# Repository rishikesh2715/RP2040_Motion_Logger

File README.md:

# RP2040 Motion Logger

<p align="center">
  <div>

  </div>
  <div>

  </div>
</p>

*I have slightly modified the board to include a bootloader button and made some aesthetic changes since having this board produced. Thus, the produced board slightly looks different. Everything else remains the same*

## Order this Board Through [PCBway](https://www.pcbway.com) 🛫

You can order this board through PCBway for excellent board quality and fast shipping at a very affordable rate. 

- Using PCBway as the manufacturer is recommended because the stackup for this board is based on their specifications. The differential impedance for the USB differential pair has been calculated based on PCBway’s stackup, ensuring that the board will perform as intended when manufactured with them.

- The Bill of Materials (BOM) provided is in PCBway's format. This compatibility ensures a smooth and reliable production experience, reducing the chances of delays due to part sourcing.

To order, simply upload the zip file to PCBway’s portal, select your preferences,
set the Min Track/spacing to 6/6 mil and set the min hole size to 0.2mm. Choosing Immersion Gold(ENIG) as the board finish is recommended but not required, and place your order. PCBway’s user-friendly interface allows for easy customization and order tracking from manufacturing to delivery.

You can learn more about PCBway at the end.

## Interactive PCB Viewer

You can view this board interactively on [KiCanvas](https://kicanvas.org/?github=https%3A%2F%2Fgithub.com%2Frishikesh2715%2FRP2040_Motion_Logger).

## Overview
The RP2040 Motion Logger is a custom microcontroller board based on the RP2040 chip, designed for motion data logging and versatile IoT applications. This compact board (0.9 x 2.48 inches) integrates a wide range of features, making it a powerful tool for projects requiring motion sensing, storage, and connectivity.

### Key Features:
- **Microcontroller**: RP2040 with dual ARM Cortex M0+ processors
- **Motion Sensor**: ICM-42688-P IMU for 6-axis motion tracking
- **Storage**: 128 Mbit Quad SPI Flash Memory and SD Card connector
- **Power Options**: USB Type-C connector or 1S LiPo/Li-ion battery
- **Battery Management**: Onboard charger for 1S LiPo/Li-ion batteries
- **LEDs**: Addressable RGB LED for user indications, plus power status LEDs for both 3.3V and 5V
- **Connectors**:
  - TC2030 JTAG Connector for programming and debugging
  - A set of pin headers including UART, I2C, SPI, ADC, and GPIO pins
- **Power Supply**: 3.3V buck converter supporting up to 2A current
- **Additional Features**: Reset and Bootloader buttons, ESD protection, USB Power, Battery Power, and 3.3V Power pins on headers

### Power Options:
The RP2040 Motion Logger can be powered either via the USB Type-C connector or a 1S LiPo/Li-ion battery. 

### Programming Options:
You can program the board through the USB Type-C connector or the TC2030 JTAG Connector.

## Getting Started
1. **Power Up**: Connect the board via USB Type-C or connect a 1S LiPo/Li-ion battery.
2. **Programming**: Use either the USB connection or JTAG connector with an appropriate debugger to flash your code. (I use VS Code with Raspberry PI PICO Extension)
3. **Bootloader Mode**: Hold down the Bootloader button while connecting the board to USB to enter bootloader mode.
4. **Data Logging**: Use the IMU and available storage to log motion data, or extend functionality via UART, I2C, SPI, and ADC pins.

## Hardware Pinout

*Note* In reality All the RP2040's GPIO Pins are capable of I2C, UART, SPI communications but I have intenionaly left some of the pins blank in the PINOUT diagram whenever I did not had a whole set of communication pins.

## PCBWay - PCB Manufacturing and Assembly

This project was proudly sponsored by **PCBWay**, a leading PCB manufacturer and assembler. They provided high-quality PCB manufacturing and assembly services, ensuring that the RP2040 Motion Logger board was produced to the highest standards. Here’s why PCBWay is a great choice for PCB production:

- **Exceptional Quality**: The PCBs produced by PCBWay have excellent build quality, with precise soldering and thorough assembly.
- **Fast Service**: PCBWay offers quick turnaround times, so your project can stay on track.
- **Comprehensive Services**: From prototyping to mass production, PCBWay provides services for all stages of PCB development, including multi-layer PCBs, advanced PCBs, flexible PCBs, and assembly services.
- **Affordable Pricing**: PCBWay offers competitive pricing without compromising quality.

If you’re looking for a reliable partner to bring your PCB projects to life, check out PCBWay [here](https://pcbway.com/g/lGOcWf). With their extensive capabilities and top-notch customer support, PCBWay is the ideal choice for makers, engineers, and businesses alike.

## License
This project is open-source, licensed under the MIT License. Feel free to modify and distribute as per the license terms.

## Contributing
Contributions are welcome! Please fork the repository, make your changes, and submit a pull request.

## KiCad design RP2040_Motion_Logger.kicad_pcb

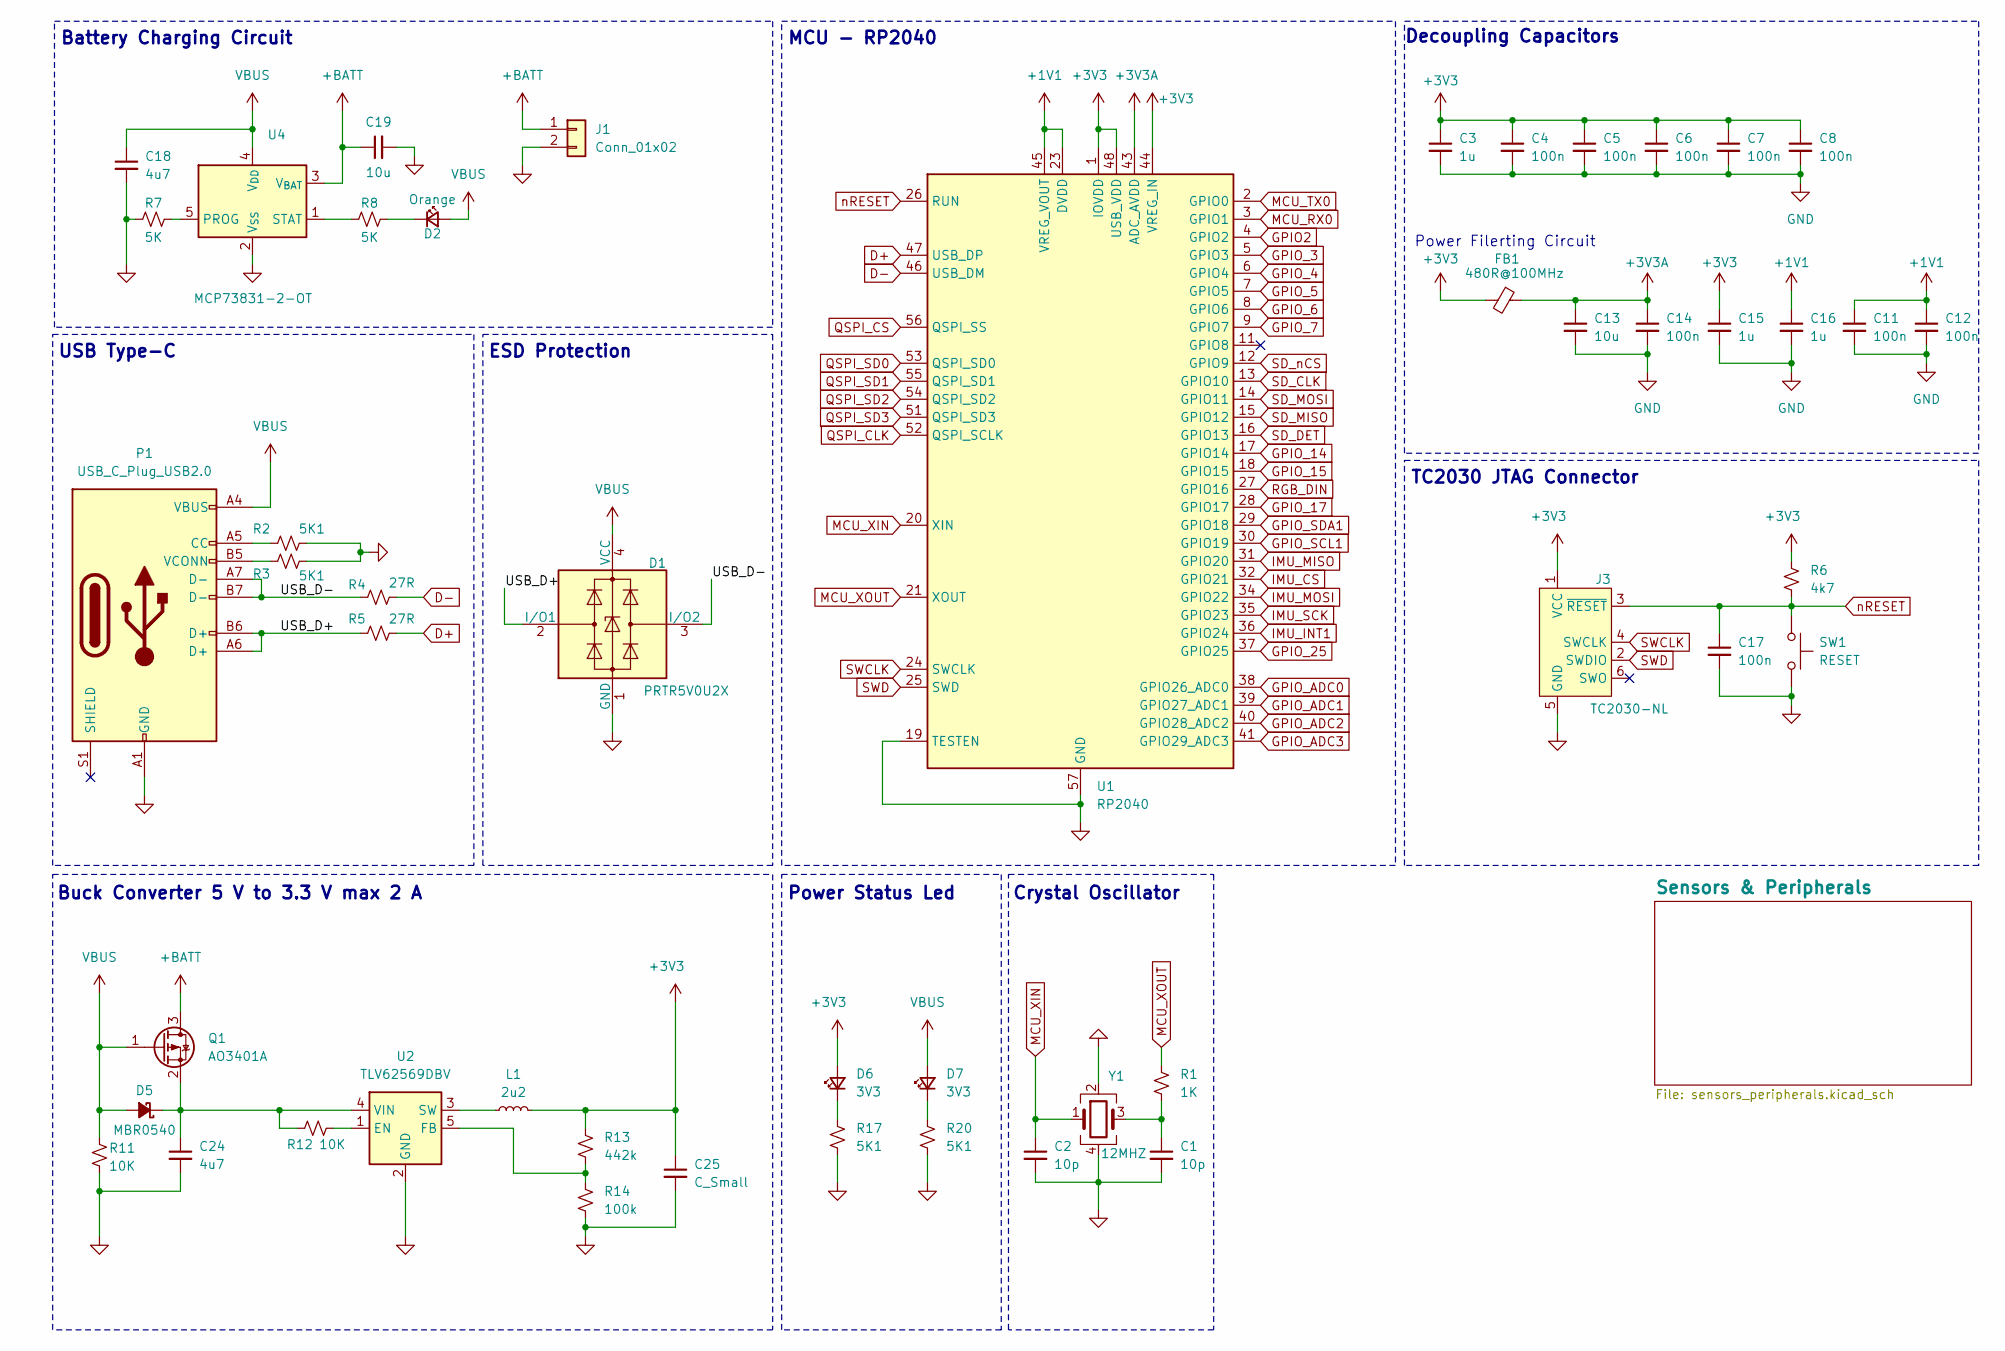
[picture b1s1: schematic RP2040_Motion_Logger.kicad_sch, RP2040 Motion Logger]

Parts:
C1, C2: 10p; C_0402_1005Metric
C3, C15, C16: 1u; C_0402_1005Metric
C4, C5, C6, C7, C8, C11, C12, C14, C17: 100n; C_0201_0603Metric
C13: 10u; C_0402_1005Metric
C18: 4u7; C_0402_1005Metric
C19: 10u; C_0603_1608Metric
C24: 4u7; C_0805_2012Metric
C25: C_Small; C_0805_2012Metric
D1: PRTR5V0U2X; SOT-143
D2: Orange; LED_0402_1005Metric
D5: MBR0540; D_1206_3216Metric
D6, D7: 3V3; LED_0402_1005Metric
FB1: 480R@100MHz; R_0402_1005Metric
J1: Conn_01x02; JST_PH_S2B-PH-K_1x02_P2.00mm_Horizontal
J3: TC2030-NL; Tag-Connect_TC2030-IDC-NL_2x03_P1.27mm_Vertical
L1: 2u2; L_Coilcraft_XAL4020-XXX
P1: USB_C_Plug_USB2.0; USB_C_Receptacle_HRO_TYPE-C-31-M-12
Q1: AO3401A; SOT-23
R1: 1K; R_0201_0603Metric
R2, R3: 5K1; R_0201_0603Metric
R4, R5: 27R; R_0201_0603Metric
R6: 4k7; R_0201_0603Metric
R7, R8: 5K; R_0402_1005Metric
R11, R12: 10K; R_0402_1005Metric
R13: 442k; R_0201_0603Metric
R14: 100k; R_0201_0603Metric
R17, R20: 5K1; R_0402_1005Metric
SW1: RESET; SW_SPST_PTS647_Sx38
U1: RP2040; QFN-56-1EP_7x7mm_P0.4mm_EP3.2x3.2mm
U2: TLV62569DBV; SOT-23-5
U4: MCP73831-2-OT; SOT-23-5
Y1: 12MHZ; Crystal_SMD_3225-4Pin_3.2x2.5mm

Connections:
+1V1: C11.1, C12.1, C16.1, U1.23 (DVDD), U1.45 (VREG_VOUT), U1.50 (DVDD)
+3V3: C3.1, C4.1, C5.1, C6.1, C7.1, C8.1, C15.1, C25.1, D6.2 (A), FB1.2, J3.1 (VCC), L1.2, R6.1, R13.1, U1.1 (IOVDD), U1.10 (IOVDD), U1.22 (IOVDD), U1.33 (IOVDD), U1.42 (IOVDD), U1.44 (VREG_IN), U1.48 (USB_VDD), U1.49 (IOVDD); also elsewhere on the board
+3V3A: C13.1, C14.1, FB1.1, U1.43 (ADC_AVDD)
+BATT: C19.1, J1.1, Q1.3 (D), U4.3 (V_{BAT}); also elsewhere on the board
/USB_D+: D1.2 (I/O1), P1.A6 (D+), P1.B6 (D+), R5.1
/USB_D-: D1.3 (I/O2), P1.A7 (D-), P1.B7 (D-), R4.1
D+: R5.2, U1.47 (USB_DP)
D-: R4.2, U1.46 (USB_DM)
GND: C1.2, C2.2, C3.2, C4.2, C5.2, C6.2, C7.2, C8.2, C11.2, C12.2, C13.2, C14.2, C15.2, C16.2, C17.2, C18.2, C19.2, C24.2, C25.2, D1.1 (GND), J1.2, J3.5 (GND), P1.A1 (GND), P1.A12 (GND), P1.B1 (GND), P1.B12 (GND), R2.2, R3.2, R7.1, R11.2, R14.2, R17.2, R20.2, SW1.2, U1.19 (TESTEN), U1.57 (GND), U2.2 (GND), U4.2 (V_{SS}), Y1.2, Y1.4; also elsewhere on the board
GPIO2: U1.4 (GPIO2); also elsewhere on the board
GPIO_3: U1.5 (GPIO3); also elsewhere on the board
GPIO_4: U1.6 (GPIO4); also elsewhere on the board
GPIO_5: U1.7 (GPIO5); also elsewhere on the board
GPIO_6: U1.8 (GPIO6); also elsewhere on the board
GPIO_7: U1.9 (GPIO7); also elsewhere on the board
GPIO_14: U1.17 (GPIO14); also elsewhere on the board
GPIO_15: U1.18 (GPIO15); also elsewhere on the board
GPIO_17: U1.28 (GPIO17); also elsewhere on the board
GPIO_25: U1.37 (GPIO25); also elsewhere on the board
GPIO_ADC0: U1.38 (GPIO26_ADC0); also elsewhere on the board
GPIO_ADC1: U1.39 (GPIO27_ADC1); also elsewhere on the board
GPIO_ADC2: U1.40 (GPIO28_ADC2); also elsewhere on the board
GPIO_ADC3: U1.41 (GPIO29_ADC3); also elsewhere on the board
GPIO_SCL1: U1.30 (GPIO19); also elsewhere on the board
GPIO_SDA1: U1.29 (GPIO18); also elsewhere on the board
IMU_CS: U1.32 (GPIO21); also elsewhere on the board
IMU_INT1: U1.36 (GPIO24); also elsewhere on the board
IMU_MISO: U1.31 (GPIO20); also elsewhere on the board
IMU_MOSI: U1.34 (GPIO22); also elsewhere on the board
IMU_SCK: U1.35 (GPIO23); also elsewhere on the board
MCU_RX0: U1.3 (GPIO1); also elsewhere on the board
MCU_TX0: U1.2 (GPIO0); also elsewhere on the board
MCU_XIN: C2.1, U1.20 (XIN), Y1.1
MCU_XOUT: R1.1, U1.21 (XOUT)
unnamed: C1.1, R1.2, Y1.3
unnamed: D2.1 (K), R8.2
unnamed: C24.1, D5.1 (K), Q1.2 (S), R12.1, U2.4 (VIN)
unnamed: D6.1 (K), R17.1
unnamed: D7.1 (K), R20.1
unnamed: P1.A5 (CC), R2.1
unnamed: P1.B5 (VCONN), R3.1
unnamed: R12.2, U2.1 (EN)
unnamed: R13.2, R14.1, U2.5 (FB)
unnamed: L1.1, U2.3 (SW)
unnamed: R7.2, U4.5 (PROG)
unnamed: R8.1, U4.1 (STAT)
QSPI_CLK: U1.52 (QSPI_SCLK); also elsewhere on the board
QSPI_CS: U1.56 (QSPI_SS); also elsewhere on the board
QSPI_SD0: U1.53 (QSPI_SD0); also elsewhere on the board
QSPI_SD1: U1.55 (QSPI_SD1); also elsewhere on the board
QSPI_SD2: U1.54 (QSPI_SD2); also elsewhere on the board
QSPI_SD3: U1.51 (QSPI_SD3); also elsewhere on the board
RGB_DIN: U1.27 (GPIO16); also elsewhere on the board
SD_CLK: U1.13 (GPIO10); also elsewhere on the board
SD_DET: U1.16 (GPIO13); also elsewhere on the board
SD_MISO: U1.15 (GPIO12); also elsewhere on the board
SD_MOSI: U1.14 (GPIO11); also elsewhere on the board
SD_nCS: U1.12 (GPIO9); also elsewhere on the board
SWCLK: J3.4 (SWCLK), U1.24 (SWCLK)
SWD: J3.2 (SWDIO), U1.25 (SWD)
VBUS: C18.1, D1.4 (VCC), D2.2 (A), D5.2 (A), D7.2 (A), P1.A4 (VBUS), P1.A9 (VBUS), P1.B4 (VBUS), P1.B9 (VBUS), Q1.1 (G), R11.1, U4.4 (V_{DD}); also elsewhere on the board
nRESET: C17.1, J3.3 (~RESET), R6.2, SW1.1, U1.26 (RUN)

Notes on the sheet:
Battery Charging Circuit
Crystal Oscillator
USB Type-C
ESD Protection
TC2030 JTAG Connector
Power Status Led
MCU - RP2040
Power Filerting Circuit
Buck Converter 5 V to 3.3 V max 2 A
Decoupling Capacitors

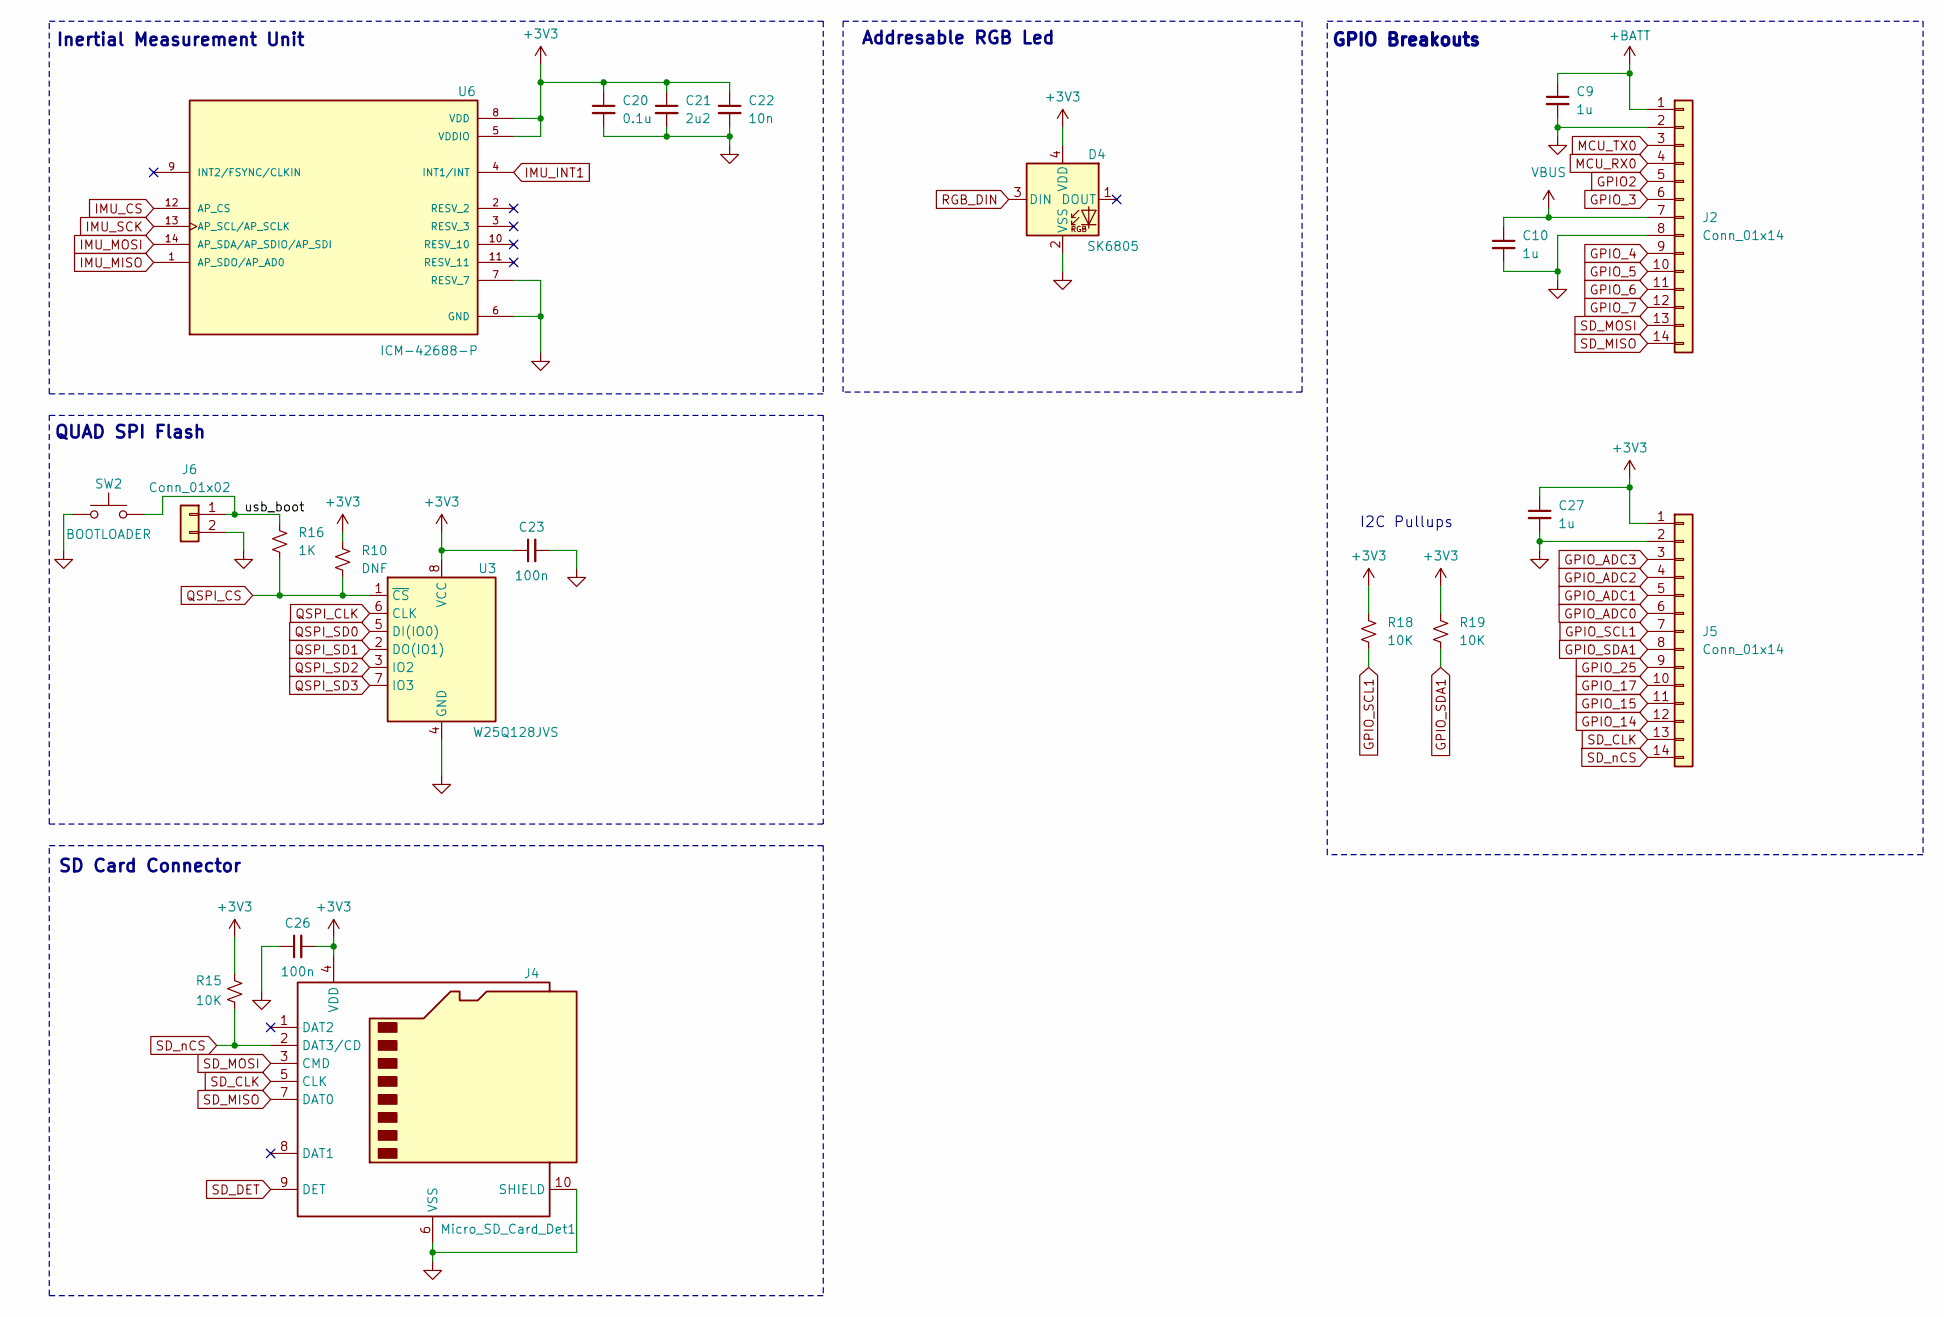
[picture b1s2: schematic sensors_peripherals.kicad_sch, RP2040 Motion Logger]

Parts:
C9, C10, C27: 1u; C_0402_1005Metric
C20: 0.1u; C_0201_0603Metric
C21: 2u2; C_0402_1005Metric
C22: 10n; C_0201_0603Metric
C23: 100n; C_0201_0603Metric
C26: 100n; C_0805_2012Metric_Pad1.18x1.45mm_HandSolder
D4: SK6805; LED_SK6805_PLCC4_2.4x2.7mm_P1.3mm
J2, J5: Conn_01x14; PinHeader_1x14_P2.54mm_Vertical
J4: Micro_SD_Card_Det1; microSD_HC_Hirose_DM3D-SF
J6: Conn_01x02; SolderJumper-2_P1.3mm_Open_TrianglePad1.0x1.5mm
R10: DNF; R_0201_0603Metric
R15: 10K; R_0805_2012Metric_Pad1.20x1.40mm_HandSolder
R16: 1K; R_0201_0603Metric
R18, R19: 10K; R_0201_0603Metric
SW2: BOOTLOADER; SW_SPST_PTS647_Sx38
U3: W25Q128JVS; SOIC-8_5.23x5.23mm_P1.27mm
U6: ICM-42688-P; PQFN50P300X250X97-14N; PARTREV 1.2

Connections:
+3V3: C20.1, C21.1, C22.1, C23.1, C26.2, C27.1, D4.4 (VDD), J4.4 (VDD), J5.1, R10.1, R15.1, R18.1, R19.1, U3.8 (VCC), U6.5 (VDDIO), U6.8 (VDD); also elsewhere on the board
+BATT: C9.1, J2.1; also elsewhere on the board
/Sensors & Peripherals/usb_boot: J6.1, R16.1, SW2.2
GND: C9.2, C10.2, C20.2, C21.2, C22.2, C23.2, C26.1, C27.2, D4.2 (VSS), J2.2, J2.8, J4.6 (VSS), J4.10 (SHIELD), J5.2, J6.2, SW2.1, U3.4 (GND), U6.6 (GND), U6.7 (RESV_7); also elsewhere on the board
GPIO2: J2.5; also elsewhere on the board
GPIO_3: J2.6; also elsewhere on the board
GPIO_4: J2.9; also elsewhere on the board
GPIO_5: J2.10; also elsewhere on the board
GPIO_6: J2.11; also elsewhere on the board
GPIO_7: J2.12; also elsewhere on the board
GPIO_14: J5.12; also elsewhere on the board
GPIO_15: J5.11; also elsewhere on the board
GPIO_17: J5.10; also elsewhere on the board
GPIO_25: J5.9; also elsewhere on the board
GPIO_ADC0: J5.6; also elsewhere on the board
GPIO_ADC1: J5.5; also elsewhere on the board
GPIO_ADC2: J5.4; also elsewhere on the board
GPIO_ADC3: J5.3; also elsewhere on the board
GPIO_SCL1: J5.7, R18.2; also elsewhere on the board
GPIO_SDA1: J5.8, R19.2; also elsewhere on the board
IMU_CS: U6.12 (AP_CS); also elsewhere on the board
IMU_INT1: U6.4 (INT1/INT); also elsewhere on the board
IMU_MISO: U6.1 (AP_SDO/AP_AD0); also elsewhere on the board
IMU_MOSI: U6.14 (AP_SDA/AP_SDIO/AP_SDI); also elsewhere on the board
IMU_SCK: U6.13 (AP_SCL/AP_SCLK); also elsewhere on the board
MCU_RX0: J2.4; also elsewhere on the board
MCU_TX0: J2.3; also elsewhere on the board
QSPI_CLK: U3.6 (CLK); also elsewhere on the board
QSPI_CS: R10.2, R16.2, U3.1 (~CS); also elsewhere on the board
QSPI_SD0: U3.5 (DI(IO0)); also elsewhere on the board
QSPI_SD1: U3.2 (DO(IO1)); also elsewhere on the board
QSPI_SD2: U3.3 (IO2); also elsewhere on the board
QSPI_SD3: U3.7 (IO3); also elsewhere on the board
RGB_DIN: D4.3 (DIN); also elsewhere on the board
SD_CLK: J4.5 (CLK), J5.13; also elsewhere on the board
SD_DET: J4.9 (DET); also elsewhere on the board
SD_MISO: J2.14, J4.7 (DAT0); also elsewhere on the board
SD_MOSI: J2.13, J4.3 (CMD); also elsewhere on the board
SD_nCS: J4.2 (DAT3/CD), J5.14, R15.2; also elsewhere on the board
VBUS: C10.1, J2.7; also elsewhere on the board

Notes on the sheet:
QUAD SPI Flash
SD Card Connector
GPIO Breakouts
I2C Pullups
Inertial Measurement Unit
Addresable RGB Led

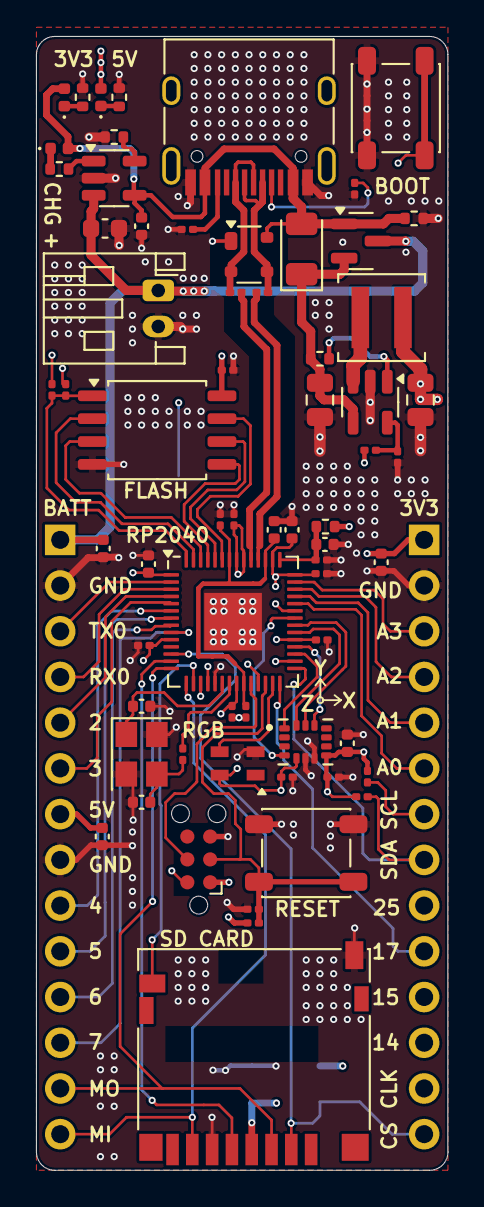
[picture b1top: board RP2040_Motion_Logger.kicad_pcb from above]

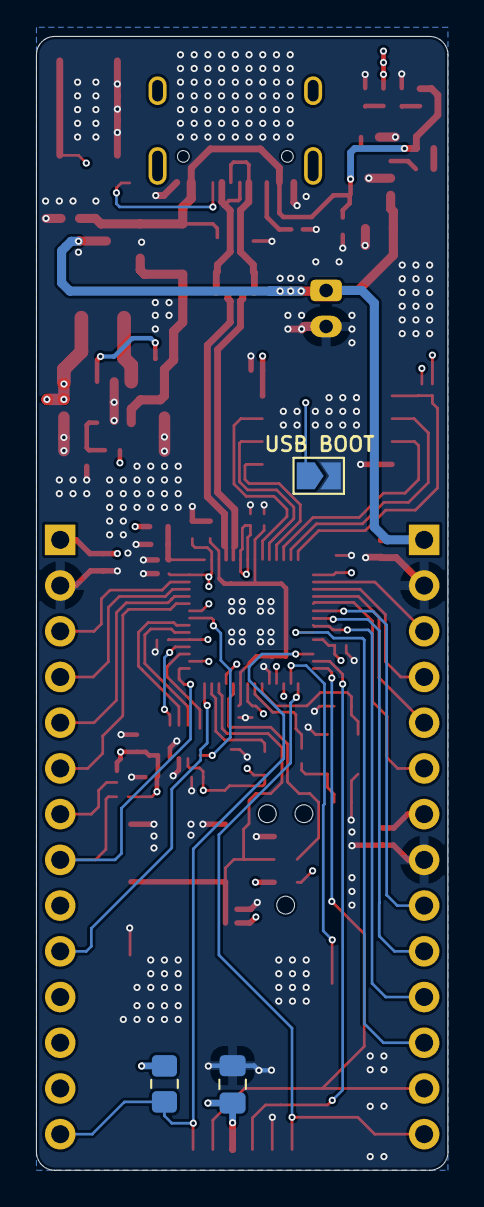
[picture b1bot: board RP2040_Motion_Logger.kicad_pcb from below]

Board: 4 copper layers, 22.9 x 63.0 mm, 70 parts (3 on the bottom side), 63 nets.

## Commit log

2024-10-02 Completed PCB
2024-10-11 made some schematic aesthetic changes
2024-10-12 Added a bootloader button and made some other QOL changes... mostly aesthetic.
2024-10-12 Remove ignored files from the repository
2024-10-12 Create LICENSE
2024-10-12 pcn images
2024-10-12 removed the DNF silkscreen for the SD Card connector's CS pin pullup resistor
2024-10-14 Production Files
2024-10-14 last commit
